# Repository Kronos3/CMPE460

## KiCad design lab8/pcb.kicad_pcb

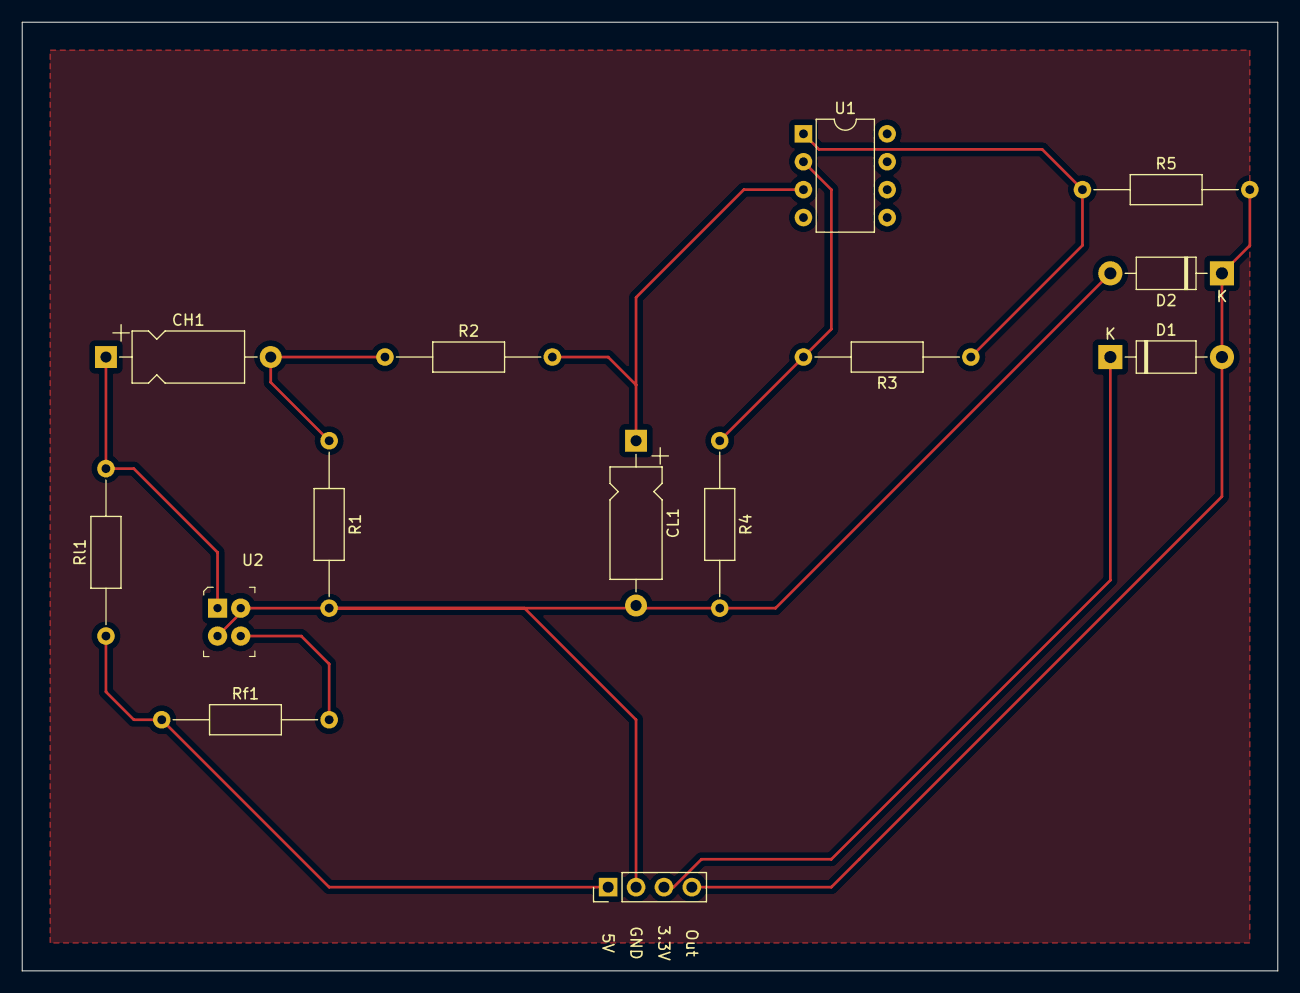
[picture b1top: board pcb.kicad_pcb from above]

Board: 2 copper layers, 114.3 x 86.4 mm, 14 parts (0 on the bottom side), 10 nets.

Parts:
CH1: 47u; CP_Axial_L10.0mm_D4.5mm_P15.00mm_Horizontal
CL1: 47u; CP_Axial_L10.0mm_D4.5mm_P15.00mm_Horizontal
D1, D2: 1N5817; D_DO-41_SOD81_P10.16mm_Horizontal
J1: Conn_01x04_Male; PinHeader_1x04_P2.54mm_Vertical
R1: 6.7k; R_Axial_DIN0207_L6.3mm_D2.5mm_P15.24mm_Horizontal
R2: 2k; R_Axial_DIN0207_L6.3mm_D2.5mm_P15.24mm_Horizontal
R3: 390k; R_Axial_DIN0207_L6.3mm_D2.5mm_P15.24mm_Horizontal
R4: 1k; R_Axial_DIN0207_L6.3mm_D2.5mm_P15.24mm_Horizontal
R5: 100; R_Axial_DIN0207_L6.3mm_D2.5mm_P15.24mm_Horizontal
Rf1: 65; R_Axial_DIN0207_L6.3mm_D2.5mm_P15.24mm_Horizontal
Rl1: 20k; R_Axial_DIN0207_L6.3mm_D2.5mm_P15.24mm_Horizontal
U1: TLC277; DIP-8_W7.62mm
U2: QRD1114; Reflective_Sensor_QRD1114

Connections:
unnamed: CH1.1, Rl1.2, U2.1
unnamed: CH1.2, R1.1, R2.1
unnamed: CL1.1, R2.2, U1.3 (+)
unnamed: CL1.2, D2.2 (A), J1.GND (Pin_2), R1.2, R4.2, U2.2, U2.4
unnamed: D1.1 (K), J1.3.3V (Pin_3)
unnamed: D1.2 (A), D2.1 (K), J1.Out (Pin_4), R5.2
unnamed: J1.5V (Pin_1), Rf1.1, Rl1.1
unnamed: R3.1, R5.1, U1.1
unnamed: R3.2, R4.1, U1.2 (-)
unnamed: Rf1.2, U2.3

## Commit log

2022-01-15 Finished labs 1 and 2
2022-01-20 Added lab4 bt
2022-01-20 Refactor reused code into libraries
2022-01-20 Cleaned up target generation
2022-01-20 Implemented oled driver
2022-01-20 Implemented I2C driver
2022-01-21 Finished lab4
2022-01-21 Wrote switch driver (with interrupts) and updated LED driver
2022-01-21 Added uartlib code
2022-01-21 Implemented tim driver
2022-01-21 Working lab5-1
2022-01-21 Fixed assertion failure format string
2022-01-21 Wrote systick driver
2022-01-22 Wrote most of the ADC initialization
2022-01-22 Fix hex conversion uprintf
2022-01-22 Working ADC
2022-02-02 Started integrating RTOS
2022-02-04 Draw line in i2c oled l4
2022-02-04 lab4 cleanup
2022-02-11 Added lab4 report
2022-02-16 Finished lab5 camera
2022-02-21 Cleaned up camera and added a process/integration time
2022-02-25 Started work on pwm, added lab5 report, added lab5 matlab
2022-02-25 Working pwm
2022-02-27 Added lab5-cam.png
2022-02-27 Finished lab5 started wrote dc driver
2022-03-02 Generalized platform
2022-03-03 Ported drivers and modules for general purpose use
2022-03-03 Fix bug
2022-03-04 Working bcm2835 build
2022-03-05 Bare minimum working on raspi
2022-03-18 Finished lab6 code
2022-03-21 Finished lab7
2022-03-23 Wrote edge detection
2022-03-23 Use convolution for derivative
2022-03-25 Finished lab8, support MSP432P4111
2022-03-26 Car mostly working
2022-03-27 Working milestone 1
2022-03-27 Clean up unused code
2022-03-27 Working motor controller
2022-04-16 Added lab8
2022-04-16 Schmitt trigger for lab8
2022-04-17 Finished lab8
